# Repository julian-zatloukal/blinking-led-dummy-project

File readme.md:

# Dummy project about a blinking LED. 
### Description
A simple microcontroller-based board that blinks an LED every 500mS.
* Toggles every 500mS.
* Based on the ATmega328P microcontroller. 
* Coded in C, compiled in avr-gcc, and written using the Atmel Studio IDE.
* Printed Circuit Board designed in Eagle (EDA).
* Simulated in Proteus VSM.

### Simulation

### Main routine
```c
#define F_CPU 16000000
#include <avr/io.h>
#include <util/delay.h>

int main(void)
{
	DDRD |= (1<<0);
	while (1) 
	{
		PORTD ^= (1<<0);
		_delay_ms(500);
	}
}
```

### Circuit schematic

### PCB Top view

### PCB Bottom view

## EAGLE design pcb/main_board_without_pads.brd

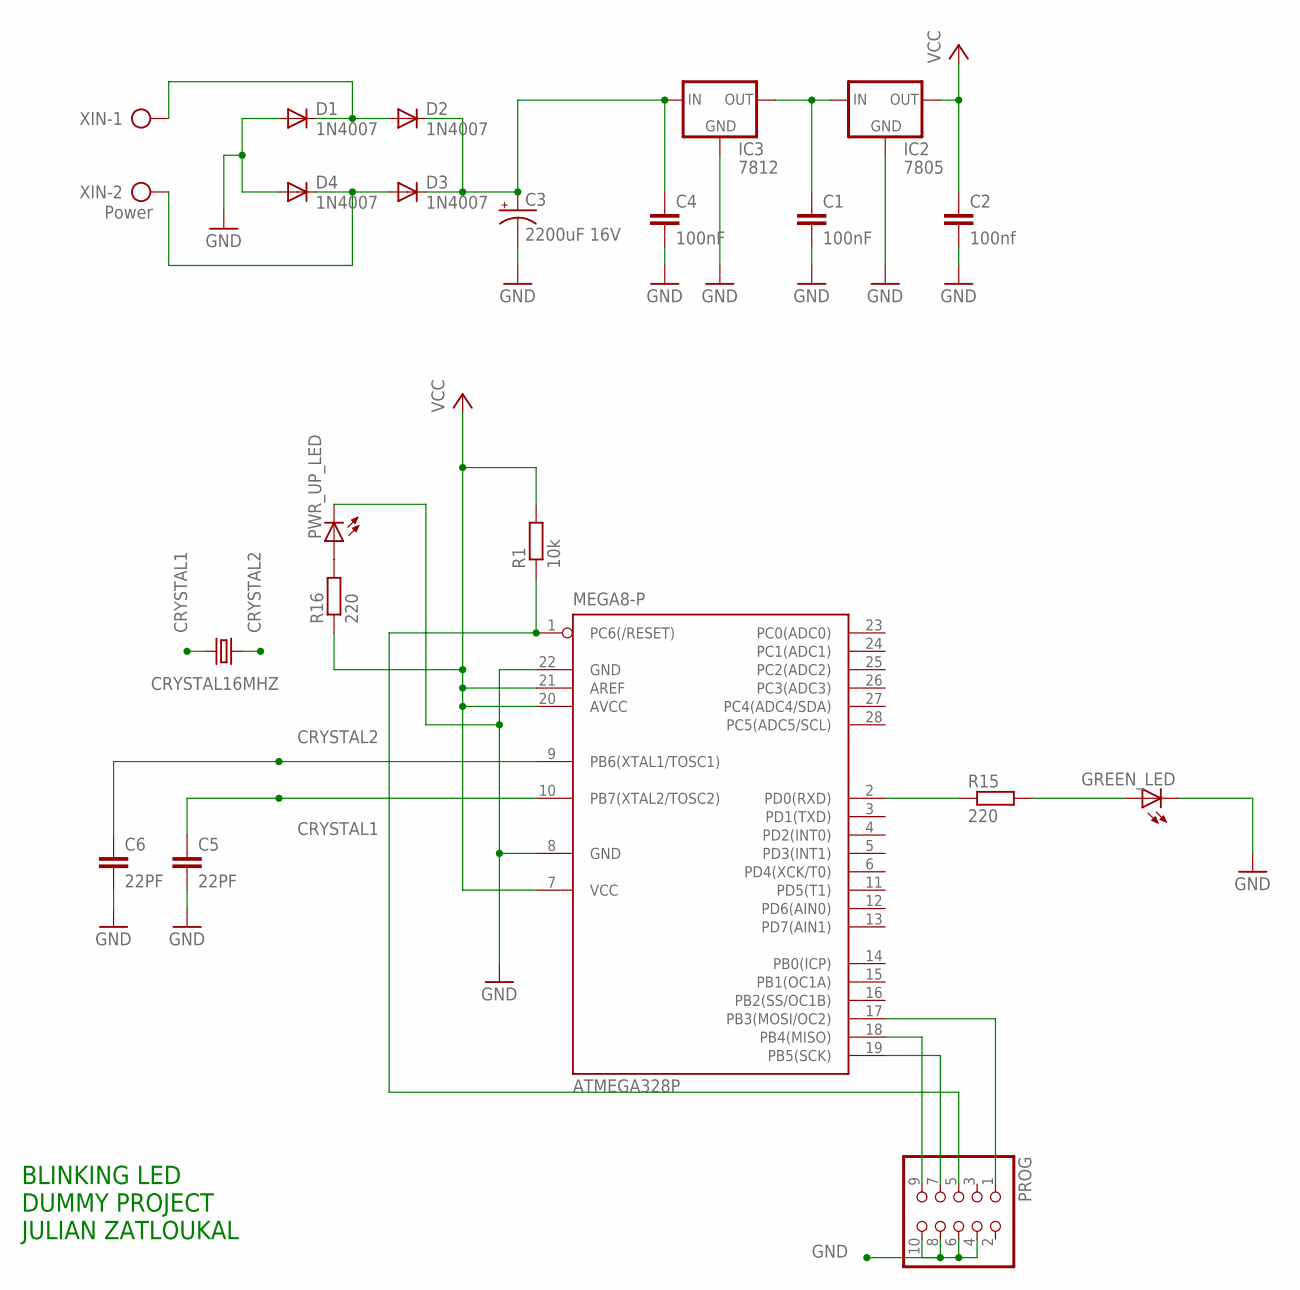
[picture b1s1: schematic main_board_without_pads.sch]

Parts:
ATMEGA328P: MEGA8-P; DIL28-3
C1, C4: 100nF; C050-025X075
C2: 100nf; C050-025X075
C3: 2200uF 16V; E7,5-16
C5, C6: 22PF; C050-024X044
CRYSTAL16MHZ: CRYSTALHC49S; HC49/S
D1, D2, D3, D4: 1N4007; DO41-10
GREEN_LED: LED5MM
IC2: 7805; 78XXL
IC3: 7812; 78XXL
PROG: PINHD-2X5; 2X05
PWR_UP_LED: LED5MM
R1: 10k; 0207/10
R15, R16: 220; 0207/10
XIN: Power; AK500/2

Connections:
+12V: C1.1, IC2.IN, IC3.OUT
CRYSTAL1: ATMEGA328P.10 (PB7(XTAL2/TOSC2)), C5.1, CRYSTAL16MHZ.2
CRYSTAL2: ATMEGA328P.9 (PB6(XTAL1/TOSC1)), C6.1, CRYSTAL16MHZ.1
GND: ATMEGA328P.8 (GND), ATMEGA328P.22 (GND), C1.2, C2.2, C3.-, C4.2, C5.2, C6.2, D1.A, D4.A, GREEN_LED.K (C), IC2.GND, IC3.GND, PROG.4, PROG.6, PROG.8, PROG.10, PWR_UP_LED.K (C)
unnamed: ATMEGA328P.1 (PC6(/RESET)), PROG.5, R1.1
unnamed: ATMEGA328P.2 (PD0(RXD)), R15.1
unnamed: ATMEGA328P.17 (PB3(MOSI/OC2)), PROG.1
unnamed: PWR_UP_LED.A, R16.2
unnamed: ATMEGA328P.19 (PB5(SCK)), PROG.7
unnamed: ATMEGA328P.18 (PB4(MISO)), PROG.9
unnamed: C3.+, C4.1, D2.C, D3.C, IC3.IN
unnamed: D1.C, D2.A, XIN.1
unnamed: D3.A, D4.C, XIN.2
unnamed: GREEN_LED.A, R15.2
VCC: ATMEGA328P.7 (VCC), ATMEGA328P.20 (AVCC), ATMEGA328P.21 (AREF), C2.1, IC2.OUT, R1.2, R16.1

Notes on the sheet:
BLINKING LED DUMMY PROJECT JULIAN ZATLOUKAL

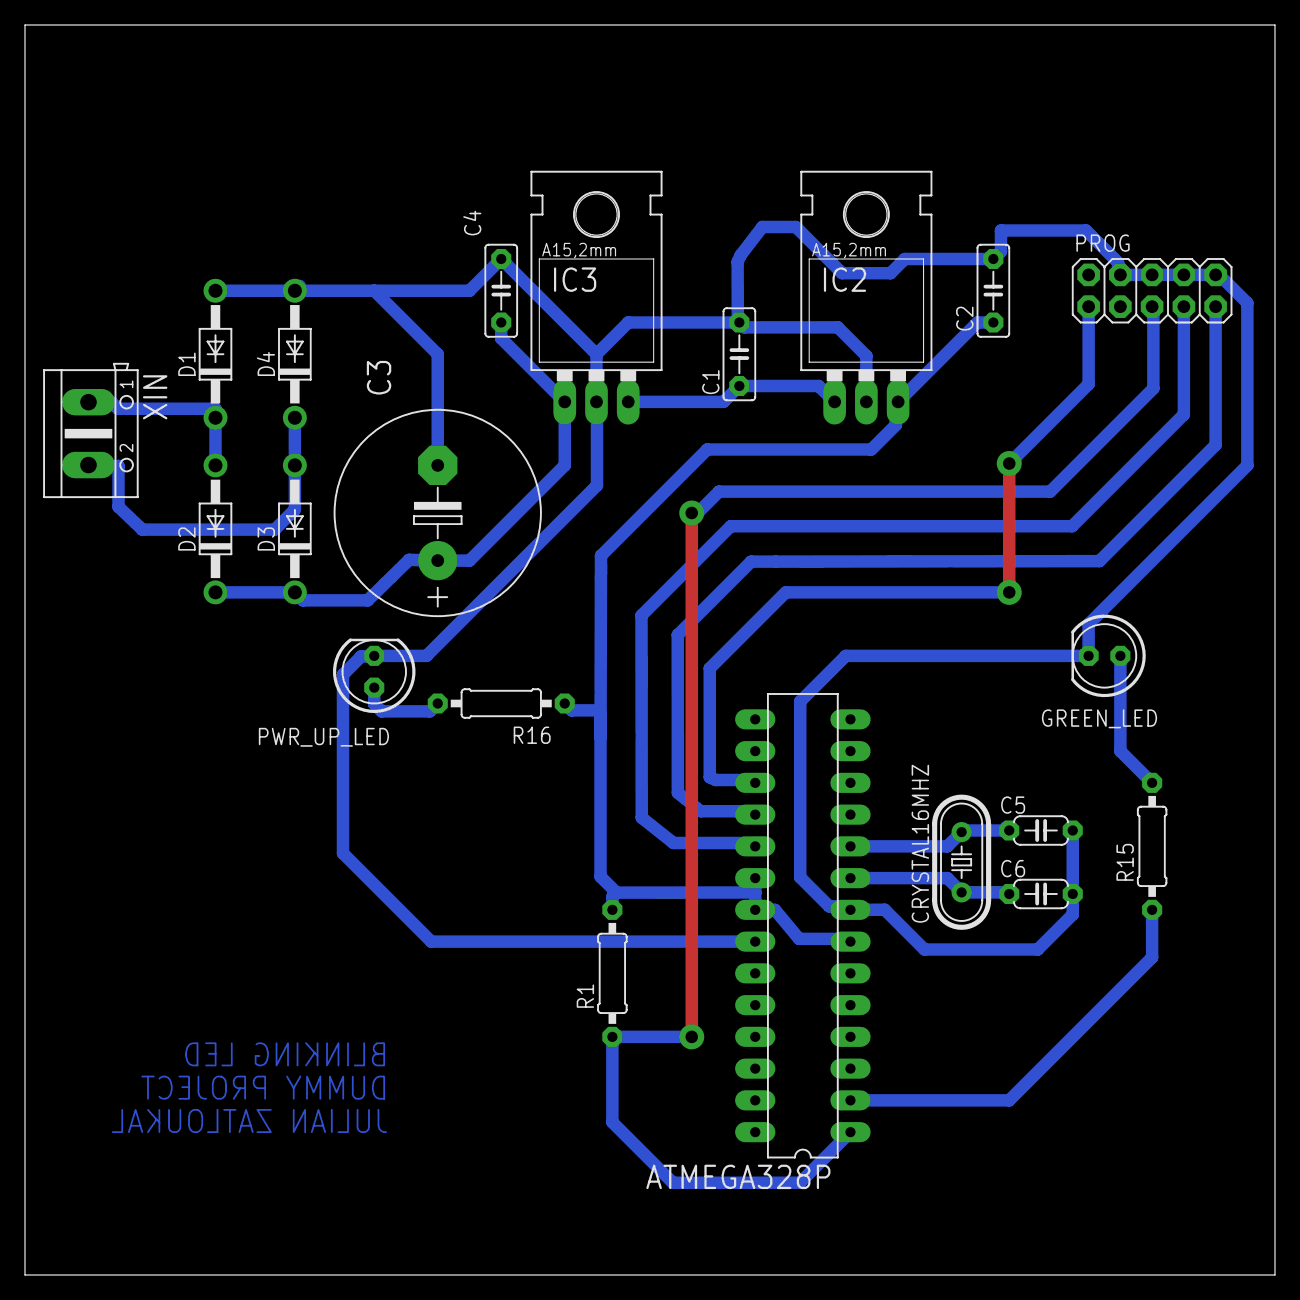
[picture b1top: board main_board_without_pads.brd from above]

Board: 2 copper layers, 100.0 x 100.0 mm, 21 parts (0 on the bottom side), 15 nets.

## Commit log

2019-11-26 Adding images
2019-11-26 Changing images
2019-11-26 Adding simulation iamges
2019-11-26 Adding code to readme
2019-11-26 Fixing margins
2019-11-26 Set theme jekyll-theme-minimal
2019-11-28 google index
2019-11-28 google index 2
2019-11-28 google index 3
2019-11-28 google index 4
2019-11-28 google index 6
2019-11-28 google index 7
